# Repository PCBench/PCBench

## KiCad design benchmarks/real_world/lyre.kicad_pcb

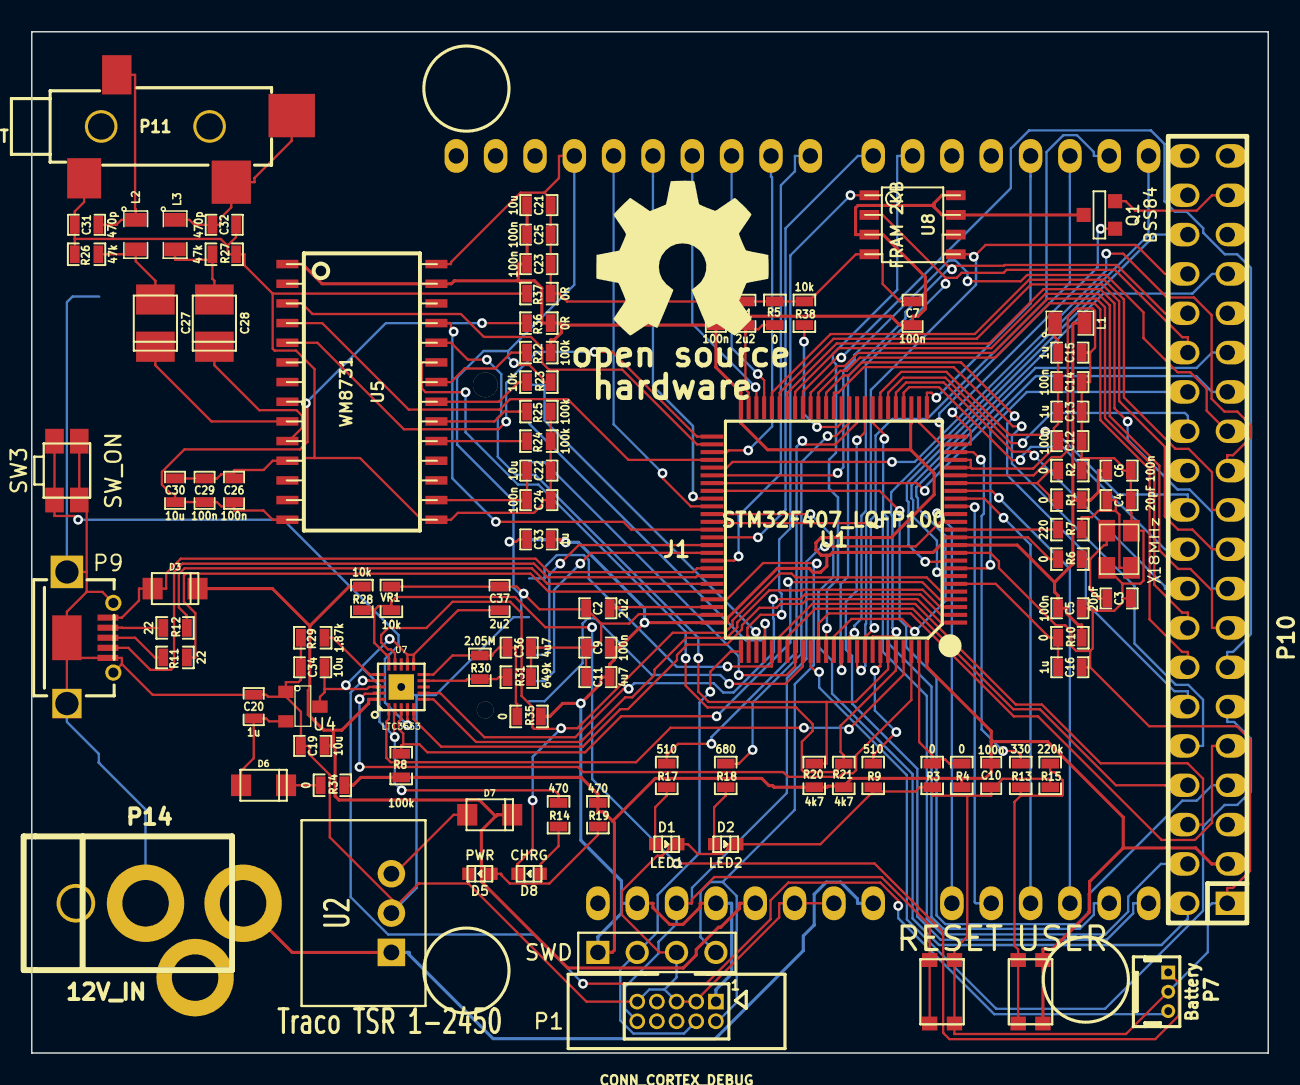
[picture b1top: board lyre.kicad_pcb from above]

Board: 2 copper layers, 79.9 x 66.0 mm, 101 parts (1 on the bottom side), 127 nets.

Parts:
C1, C2, C37: 2u2; SM0603_Capa
C3, C4: 20pF; SM0603_Capa
C5, C6, C7, C8, C9, C10, C12, C14, C23, C24, C25, C26, C29: 100n; SM0603_Capa
C11, C36: 4u7; SM0603_Capa
C13, C15, C16, C20, C33: 1u; SM0603_Capa
C19, C21, C22, C30, C34: 10u; SM0603_Capa
C27, C28: 220u; c_tant_B
C31, C32: 470p; SM0603_Capa
D1: LED1; Led_0603
D2: LED2; Led_0603
D3, D6, D7: DIODE; do219ab
D5: PWR; Led_0603
D8: CHRG; Led_0603
J1: ARDUINO_HEADER; arduino_header_bare
L1: L_MINI; SM0805
L2, L3: INDUCTOR_SMALL; SM0805
M1: LOGO_OSHW; OSHW_logo_2
P1: SWD; pin_header_2.54mm_1x4
P7: Battery; BATTery_Molex_53047-0310
P8: CONN_CORTEX_DEBUG; Pin_Array_5x2_1.27mm_RMC
P9: USBCONN-HOSTCAPABLE; USB_MICRO_RMC
P10: LCD_2.4_INCH; pin_socket_20x2
P11: STEREO-AUDIO-JACK_SJ1-3524-SMT; SJ-3524-SMT_Stereo_Jack
P13: CONN_SD; Memory_Card_SD_3M
P14: 12V_IN; JACK_PWR
Q1: BSS84; SOT23GDS
R1, R2, R3, R4, R5, R6, R10, R34, R35: 0; SM0603_Resistor
R7: 220; SM0603_Resistor
R8, R22, R24, R25: 100k; SM0603_Resistor
R9, R17: 510; SM0603_Resistor
R11, R12: 22; SM0603_Resistor
R13: 330; SM0603_Resistor
R14, R19: 470; SM0603_Resistor
R15: 220k; SM0603_Resistor
R18: 680; SM0603_Resistor
R20, R21: 4k7; SM0603_Resistor
R23, R28, R38: 10k; SM0603_Resistor
R26, R27: 47k; SM0603_Resistor
R29: 1.87k; SM0603_Resistor
R30: 2.05M; SM0603_Resistor
R31: 649k; SM0603_Resistor
R36, R37: 0R; SM0603_Resistor
SW1: USER; SW_C&K_KMR4
SW2: RESET; SW_C&K_KMR4
SW3: SW_ON; sw_panasonic_evqp7
U1: STM32F407_LQFP100; LQFP100_0.5mm_SOT407-1_LPC1768
U2: Traco TSR 1-2450; Traco_TSR-1
U4: MCP1703_SOT23; SOT23
U5: WM8731; soic-28
U7: LTC3553; qfn-20-LTC3553
U8: FRAM 2KB; so-8
VR1: 10k; SM0603_Resistor
X1: 8MHz; XTAL-3.2x2.5mm

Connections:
+5V: C19.1, D3.2, D7.2, J1.5, R28.1, U7.20
+12V: J1.8, P14.1, U2.1
/CPU/PB2: R38.2, U1.37
/CPU/VBAT: C16.1, R10.1, U1.6
/CPU/VDDA: C12.1, C13.1, C14.1, C15.1, L1.1, U1.21, U1.22
/LCD/LED_A: P10.37, Q1.S
/Power/BAT_THERMISTOR: P7.1, R28.2, U7.15, VR1.1
/Power/V_BAT: P7.3, U7.17
/Power/V_OUT: C34.1, C37.1, R14.1, U4.3, U7.2, U7.11, U7.12, U7.18
AGND_AUDIO: C22.2, C24.2, C26.2, C29.2, C30.2, C31.2, C32.2, P11.1, R24.1, R25.1, R26.2, R27.2, R37.2, U5.11, U5.15
AUDIO_SCL: R20.2, U1.95, U5.24
AUDIO_SDA: R21.2, U1.96, U5.23
AVDD: C26.1, C29.1, C30.1, R36.2, U5.8, U5.14
BOOT0: R9.1, U1.94
BTN_USER: R13.1, U1.23
BUCK_ON: U1.2, U7.7
D0: P10.2, U1.61
D1: P10.4, U1.62
D2: P10.6, U1.81
D3: P10.8, U1.82
D4: P10.10, U1.38
D5: P10.12, U1.39
D6: P10.14, U1.40
D7: P10.16, U1.41
D8: P10.13, U1.42
D9: P10.15, U1.43
D10: P10.17, U1.44
D11: P10.19, U1.45
D12: P10.21, U1.46
D13: P10.23, U1.55
D14: P10.25, U1.56
D15: P10.27, U1.57
GND: C1.2, C2.2, C3.2, C4.2, C5.2, C6.2, C7.2, C8.2, C9.2, C10.2, C11.2, C12.2, C13.2, C14.2, C15.2, C16.2, C19.2, C20.2, C21.2, C23.2, C25.2, C33.2, C34.2, C36.2, C37.2, D1.2, D2.2, D5.2, J1.6, J1.7, J1.29, P1.3, P7.2, P8.3, P8.5, P8.9, P9.4, P9.5, P10.1, P13.3, P13.6, P13.16, P13.17, P14.2, R2.2, R3.2, R5.2, R9.2, R15.2, R23.2, R29.2, R31.2, R37.1, R38.1, SW2.2, SW3.1, U1.10, U1.20, U1.27, U1.74, U2.2, U4.1, U5.28, U7.21, U8.4, VR1.2, X1.2, X1.4
HPWR: U1.97, U7.1
I2S_MCK: U1.63, U5.25
I2S_SCK: U1.52, U5.3
I2S_SD: U1.54, U5.4
I2S_WS: U1.51, U5.5
JTCK_SWCLK: P1.2, P8.4, U1.76
JTMS_SWDIO: P1.4, P8.2, U1.72
LCD_CS: P10.29, U1.88
LCD_RD: P10.11, U1.85
LCD_RS: P10.7, U1.58
LCD_RST: P10.33, U1.7
LCD_WR: P10.9, U1.86
LDO_ON: U1.1, U7.5
LED1: R17.1, U1.35
LED2: R18.1, U1.36
LED_PWM: Q1.G, U1.24
unnamed: R7.1, U1.13
unnamed: R6.1, U1.12
unnamed: C3.1, R6.2, X1.1
unnamed: C4.1, R7.2, X1.3
unnamed: R3.1, R4.1, U1.99
unnamed: R1.1, R2.1, U1.19
unnamed: C2.1, U1.73
unnamed: C1.1, R5.1, U1.49
unnamed: C31.1, L2.1, P11.3
unnamed: C28.1, U5.10
unnamed: C27.1, U5.9
unnamed: R24.2, U5.19
unnamed: R25.2, U5.20
unnamed: C28.2, L3.2, R27.1
unnamed: C27.2, L2.2, R26.1
unnamed: C32.1, L3.1, P11.2, P11.4
unnamed: C22.1, C24.1, U5.16
unnamed: R23.1, U5.21
unnamed: R22.2, U5.22
unnamed: D5.1, R19.2
unnamed: D6.2, R34.1
unnamed: R30.2, R31.1, U7.9
unnamed: SW3.2, U7.4
unnamed: R29.1, U7.16
unnamed: C20.1, D6.1, U4.2
unnamed: C36.1, R30.1, R35.1, U7.10
unnamed: D8.1, R14.2
unnamed: D7.1, U2.3
unnamed: P9.2, R12.1
unnamed: P9.3, R11.2
unnamed: R13.2, R15.1, SW1.2
unnamed: D1.1, R17.2
unnamed: D2.1, R18.2
NRST: J1.3, P8.10, SW2.1, U1.14
OTG_FS_DM: R12.2, U1.70
OTG_FS_DP: R11.1, U1.71
OTG_FS_ID: P9.6, U1.69
PA2: J1.17, U1.25
PA3: J1.18, U1.26
PA8: J1.23, U1.67
PB10: J1.25, U1.47
PB11: J1.26, U1.48
PB14: J1.24, U1.53
PBSTAT: R8.2, U1.4, U7.3
PC0: J1.9, U1.15
PC1: J1.10, U1.16
PC2: J1.11, U1.17
PC3: J1.12, U1.18
PC4: J1.13, U1.33
PC5: J1.14, U1.34
PC7: J1.22, U1.64
PD6: J1.21, U1.87
PD12: J1.27, U1.59
PD13: J1.28, U1.60
SDIO_CK: P13.5, U1.80
SDIO_CMD: P13.2, U1.83
SDIO_D0: P13.7, U1.65
SDIO_D1: P13.8, U1.66
SDIO_D2: P13.9, U1.78
SDIO_D3: P13.1, U1.79
SD_CARD_DET: P13.15, U1.84
SD_SS: P10.36, U1.9
SPI1_MISO: P10.26, U1.31
SPI1_MOSI: P10.22, U1.32
SPI1_SCK: P10.18, U1.30
SPI1_SS: P10.20, U1.29
SPI3_MISO: P10.30, U1.90, U8.2
SPI3_MOSI: P10.34, U1.91, U8.5
SPI3_SCK: P10.32, U1.89, U8.6
SPI3_SS: U1.77, U8.1
STBY: U1.3, U7.6
SUSP: U1.98, U7.19
TP_INT: P10.28, U1.8
UART1_RX: J1.15, U1.93
UART1_TX: J1.16, U1.92
VBUS_FS: D3.1, P9.1, U1.68
VDD: C5.1, C6.1, C7.1, C8.1, C9.1, C10.1, C11.1, C21.1, C23.1, C25.1, C33.1, J1.2, J1.4, L1.2, P1.1, P8.1, P10.3, P13.4, Q1.D, R1.2, R4.2, R8.1, R10.2, R19.1, R20.1, R21.1, R22.1, R34.2, R35.2, R36.1, SW1.1, U1.11, U1.28, U1.50, U1.75, U1.100, U5.1, U5.27, U8.3, U8.7, U8.8
nCHRG: D8.2, U1.5, U7.14

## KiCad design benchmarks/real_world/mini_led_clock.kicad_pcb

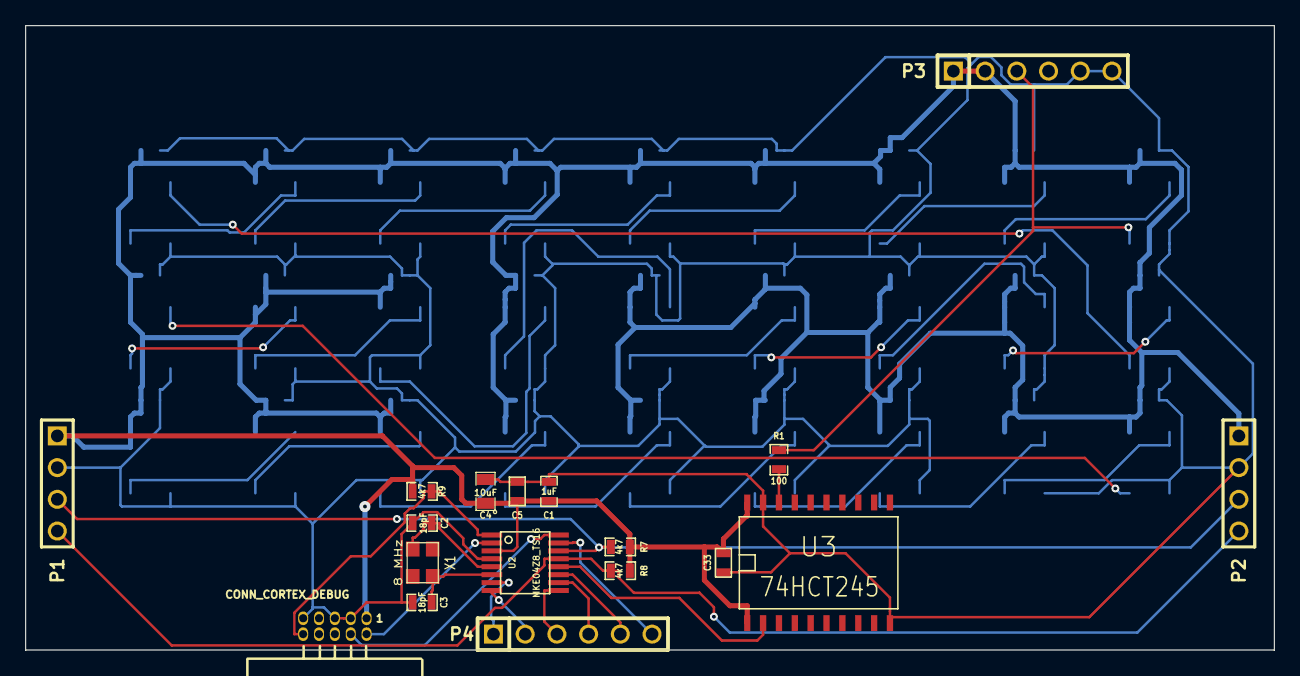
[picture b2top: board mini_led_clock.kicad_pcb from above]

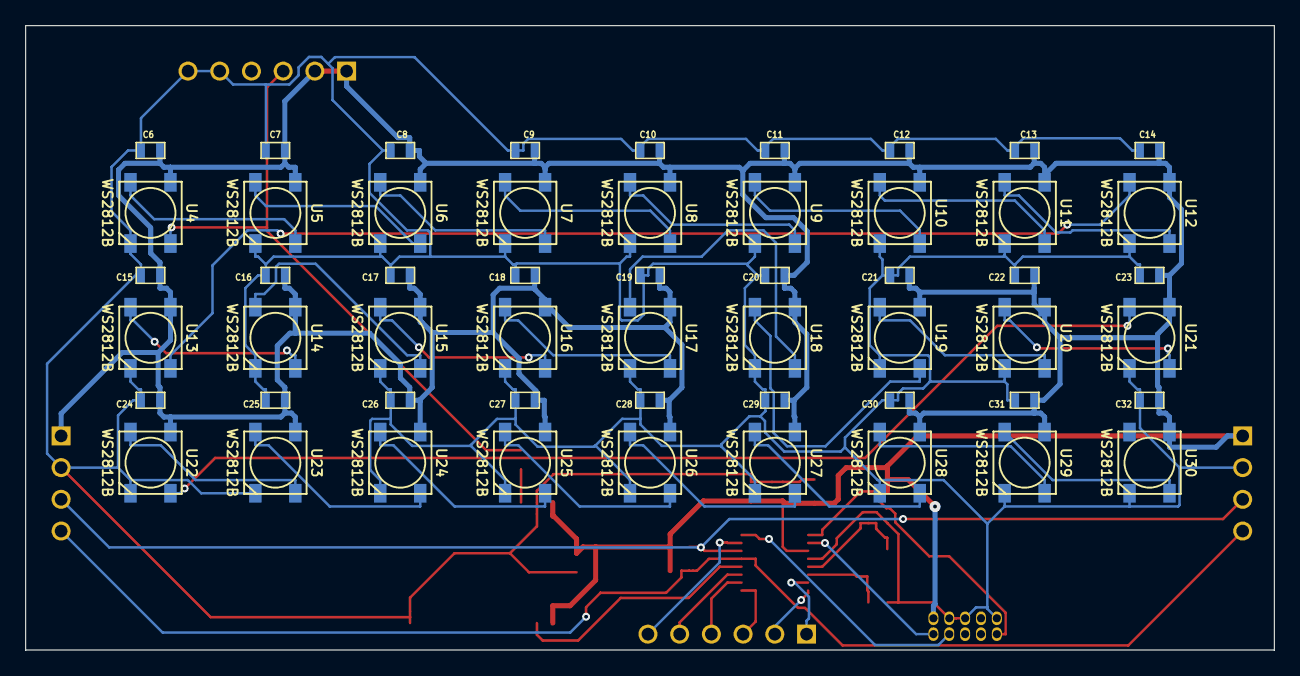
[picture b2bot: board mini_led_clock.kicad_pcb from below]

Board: 2 copper layers, 100.0 x 50.0 mm, 72 parts (54 on the bottom side), 44 nets.

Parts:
C1: 1uF; SM0603_Capa
C2, C3: 18pF; SM0603_Capa
C4: 10uF; SM0805
C5, C6, C7, C8, C9, C10, C11, C12, C13, C14, C15, C16, C17, C18, C19, C20, C21, C22, C23, C24, C25, C26, C27, C28, C29, C30, C31, C32, C33: 100nF; SM0603
P1, P2: CONN_4; PIN_ARRAY_4x1
P3, P4: CONN_6; PIN_ARRAY-6X1
R1: 100; SM0603_Resistor
R7, R8, R9: 4k7; SM0603_Resistor
U1: CONN_CORTEX_DEBUG; Pin_Array_5x2_1.27mm_RA_RMC
U2: MKE04Z8_TS16; ssop-16
U3: 74HCT245; SO20L
U4, U5, U6, U7, U8, U9, U10, U11, U12, U13, U14, U15, U16, U17, U18, U19, U20, U21, U22, U23, U24, U25, U26, U27, U28, U29, U30: WS2812B
X1: 8 MHz; XTAL-3.2x2.5mm

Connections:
/A1: P4.6, U2.15
/B1: P4.5, U2.11
/B2: P4.4, U2.10
/B3: P4.3, U2.9
/B4: P4.2, U2.8
/B5: P4.1, U2.7
/EXTAL: C2.2, U2.5, X1.1
/SCL: P1.4, P2.4, R8.1, U2.13
/SDA: P1.3, P2.3, R7.1, U2.14
/SWD_CLK: U1.4, U2.16
/SWD_DIO: U1.2, U2.2
/XTAL: C3.2, U2.6, X1.3
/nRESET: R9.1, U1.10, U2.1
GND: C1.2, C2.1, C3.1, C4.2, C5.2, C6.2, C7.2, C8.2, C9.2, C10.2, C11.2, C12.2, C13.2, C14.2, C15.2, C16.2, C17.2, C18.2, C19.2, C20.2, C21.2, C22.2, C23.2, C24.2, C25.2, C26.2, C27.2, C28.2, C29.2, C30.2, C31.2, C32.2, C33.2, P1.2, P2.2, P3.5, P3.6, U1.3, U1.5, U1.9, U2.4, U3.10, U3.19, U4.3, U5.3, U6.3, U7.3, U8.3, U9.3, U10.3, U11.3, U12.3, U13.3, U14.3, U15.3, U16.3, U17.3, U18.3, U19.3, U20.3, U21.3, U22.3, U23.3, U24.3, U25.3, U26.3, U27.3, U28.3, U29.3, U30.3
LED_DATA: P3.3, R1.2, U4.4
unnamed: R1.1, U3.18
unnamed: U2.12, U3.2
unnamed: U22.2, U23.4
unnamed: U23.2, U24.4
unnamed: U21.2, U22.4
unnamed: U19.2, U20.4
unnamed: U20.2, U21.4
unnamed: U18.2, U19.4
unnamed: U29.2, U30.4
unnamed: U27.2, U28.4
unnamed: U28.2, U29.4
unnamed: U24.2, U25.4
unnamed: U25.2, U26.4
unnamed: U26.2, U27.4
unnamed: U9.2, U10.4
unnamed: U8.2, U9.4
unnamed: U6.2, U7.4
unnamed: U7.2, U8.4
unnamed: U10.2, U11.4
unnamed: U5.2, U6.4
unnamed: U4.2, U5.4
unnamed: U14.2, U15.4
unnamed: U17.2, U18.4
unnamed: U15.2, U16.4
unnamed: U16.2, U17.4
unnamed: U12.2, U13.4
unnamed: U11.2, U12.4
unnamed: U13.2, U14.4
VCC: C1.1, C4.1, C5.1, C6.1, C7.1, C8.1, C9.1, C10.1, C11.1, C12.1, C13.1, C14.1, C15.1, C16.1, C17.1, C18.1, C19.1, C20.1, C21.1, C22.1, C23.1, C24.1, C25.1, C26.1, C27.1, C28.1, C29.1, C30.1, C31.1, C32.1, C33.1, P1.1, P2.1, P3.1, P3.2, R7.2, R8.2, R9.2, U1.1, U2.3, U3.1, U3.20, U4.1, U5.1, U6.1, U7.1, U8.1, U9.1, U10.1, U11.1, U12.1, U13.1, U14.1, U15.1, U16.1, U17.1, U18.1, U19.1, U20.1, U21.1, U22.1, U23.1, U24.1, U25.1, U26.1, U27.1, U28.1, U29.1, U30.1

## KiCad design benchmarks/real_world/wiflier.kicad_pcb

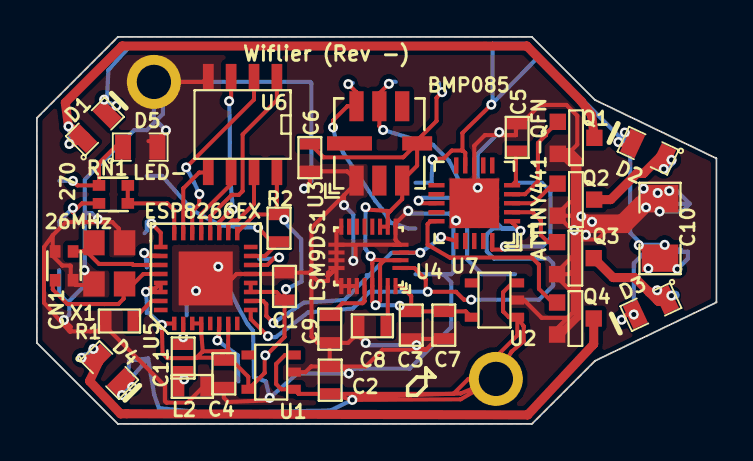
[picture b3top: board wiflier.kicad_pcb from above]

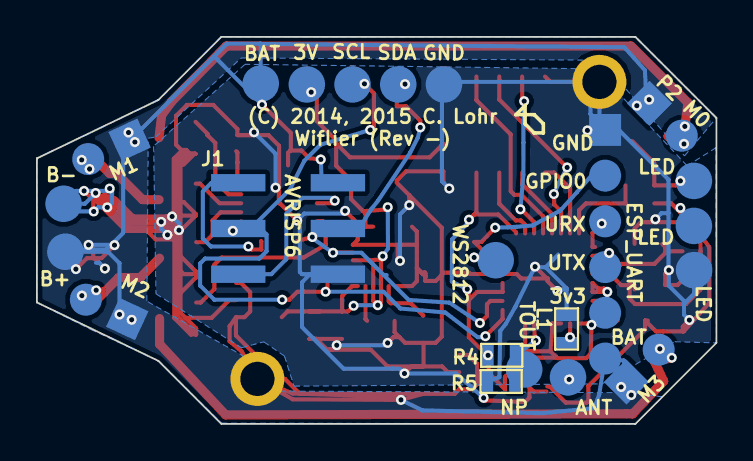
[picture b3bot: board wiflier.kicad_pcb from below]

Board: 2 copper layers, 37.8 x 21.5 mm, 57 parts (22 on the bottom side), 38 nets.

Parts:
C1, C2, C3: 10uF; SM0603
C4: 1uF; SM0603
C5: 1u; SM0603
C6, C7, C8: .1u; SM0603
C9: 10nF; SM0603
C10: 100uF; SM1206
C11: 5.6pF; SM0603
CN1: 10p; NETWORK0606
D1, D2, D3, D4: 20V_500mA; SM0805
D5: LED-; SM0805
J1: AVRISP6; RIBBON6SMT
L1, L2: NP; SM0603
P1: WS2812; .1SMTPIN
P2: M0; SMT_1x2
P3: M1; SMT_1x2
P4: M2; SMT_1x2
P5: M3; SMT_1x2
P6: ANT; .1SMTPIN
P7, P8: HOLE-1.9MM
P9: SDA; .1SMTPIN
P10: SCL; .1SMTPIN
P11: 3V; .1SMTPIN
P12: GND; .1SMTPIN
P13, P14, P15: LED; .1SMTPIN
P16: BAT; .1SMTPIN
P17: TOUT; .1SMTPIN
P21: B+; .1SMTPIN
P24: B-; .1SMTPIN
P32: ESP_UART; SMT_1x6
Q1, Q2, Q3, Q4: 7A_20V; SOT23GDS
R1, R2, R4: 12k; SM0603
R5: NP; SM0603
RN1: 270; NETWORK0606
U1, U2: MCP1824/3.0; SOT23-5
U3: BMP085
U4: LSM9DS1; LGA-24B
U5: ESP8266EX; QFN32
U6: W25Q80DV; SO8E
U7: ATTINY441-QFN; QFN20
X1: 26MHz; XTAL4P

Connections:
+3.3V: C1.1, C4.1, P32.5, R2.2, R4.1, U1.5, U5.1, U5.3, U5.4, U5.7, U5.11, U5.12, U5.17, U5.29, U5.30, U6.8
+3.3VP: C3.1, C6.2, C7.1, P11.1, U2.5, U3.3, U3.4, U4.1, U4.3, U4.7, U4.8, U4.22, U4.23
+BATT: C2.1, C10.1, D1.2, D2.2, D3.2, D4.2, J1.2, P2.1, P3.1, P4.1, P5.1, P8.1, P16.1, P21.1, P32.6, U1.1, U1.3, U2.1, U2.3, U7.9
AVRMISO: J1.1, U7.20
AVRRST: J1.5, U7.13
GND: C1.2, C2.2, C3.2, C4.2, C5.1, C6.1, C7.2, C8.1, C9.1, C10.2, CN1.2, CN1.3, D5.2, J1.6, L1.2, L2.2, P7.1, P12.1, P15.1, P24.1, P32.1, Q1.S, Q2.S, Q3.S, Q4.S, R1.1, R5.2, U1.2, U2.2, U3.1, U4.5, U4.6, U4.13, U4.14, U4.15, U4.16, U4.17, U4.18, U4.19, U4.20, U5.13, U5.33, U6.4, U7.8, U7.21, X1.3, X1.4
GP5: RN1.1, RN1.3, U5.24
GPIO0: P32.2, R2.1, U5.15
GPIO2: P1.1, U5.14
M0P: D1.1, P2.2, Q1.D
M1P: D2.1, P3.2, Q2.D
M2P: D3.1, P4.2, Q3.D
M3P: D4.1, P5.2, Q4.D
MTR0: Q1.G, U7.4
MTR1: Q2.G, U7.3
MTR2: Q3.G, U7.2
MTR3: Q4.G, U7.15
unnamed: C11.1, L1.1, U5.2
unnamed: C11.2, L2.1, P6.1
unnamed: CN1.1, U5.28, X1.2
unnamed: R1.2, U5.31
unnamed: CN1.4, U5.27, X1.1
unnamed: C8.2, U4.24
unnamed: C9.2, U4.21
unnamed: P13.1, RN1.2
unnamed: D5.1, P14.1, RN1.4
unnamed: C5.2, U7.5
unnamed: U5.22, U6.2
unnamed: U5.23, U6.5
unnamed: U5.19, U6.3
unnamed: U5.18, U6.7
unnamed: U5.20, U6.1
unnamed: U5.21, U6.6
SCL: J1.3, P10.1, U3.6, U4.2, U5.9, U7.1
SDA: J1.4, P9.1, U3.7, U4.4, U5.10, U7.16
TOUT: P17.1, R4.2, R5.1, U5.6
URX: P32.3, U5.25
UTX: P32.4, U5.26

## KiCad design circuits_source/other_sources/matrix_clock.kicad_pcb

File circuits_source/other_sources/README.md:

This folder contains circuit source files from any other sources except Adafruit, Sparkfun, Crowdsupply and Kitspace. Note that if the souce file is from KiCAD version 5, please put `.kicad_pcb` file in this folder, and if the source file is from KiCAD version 6, please put `.kicad_pcb` and `.pro` file in this folder.

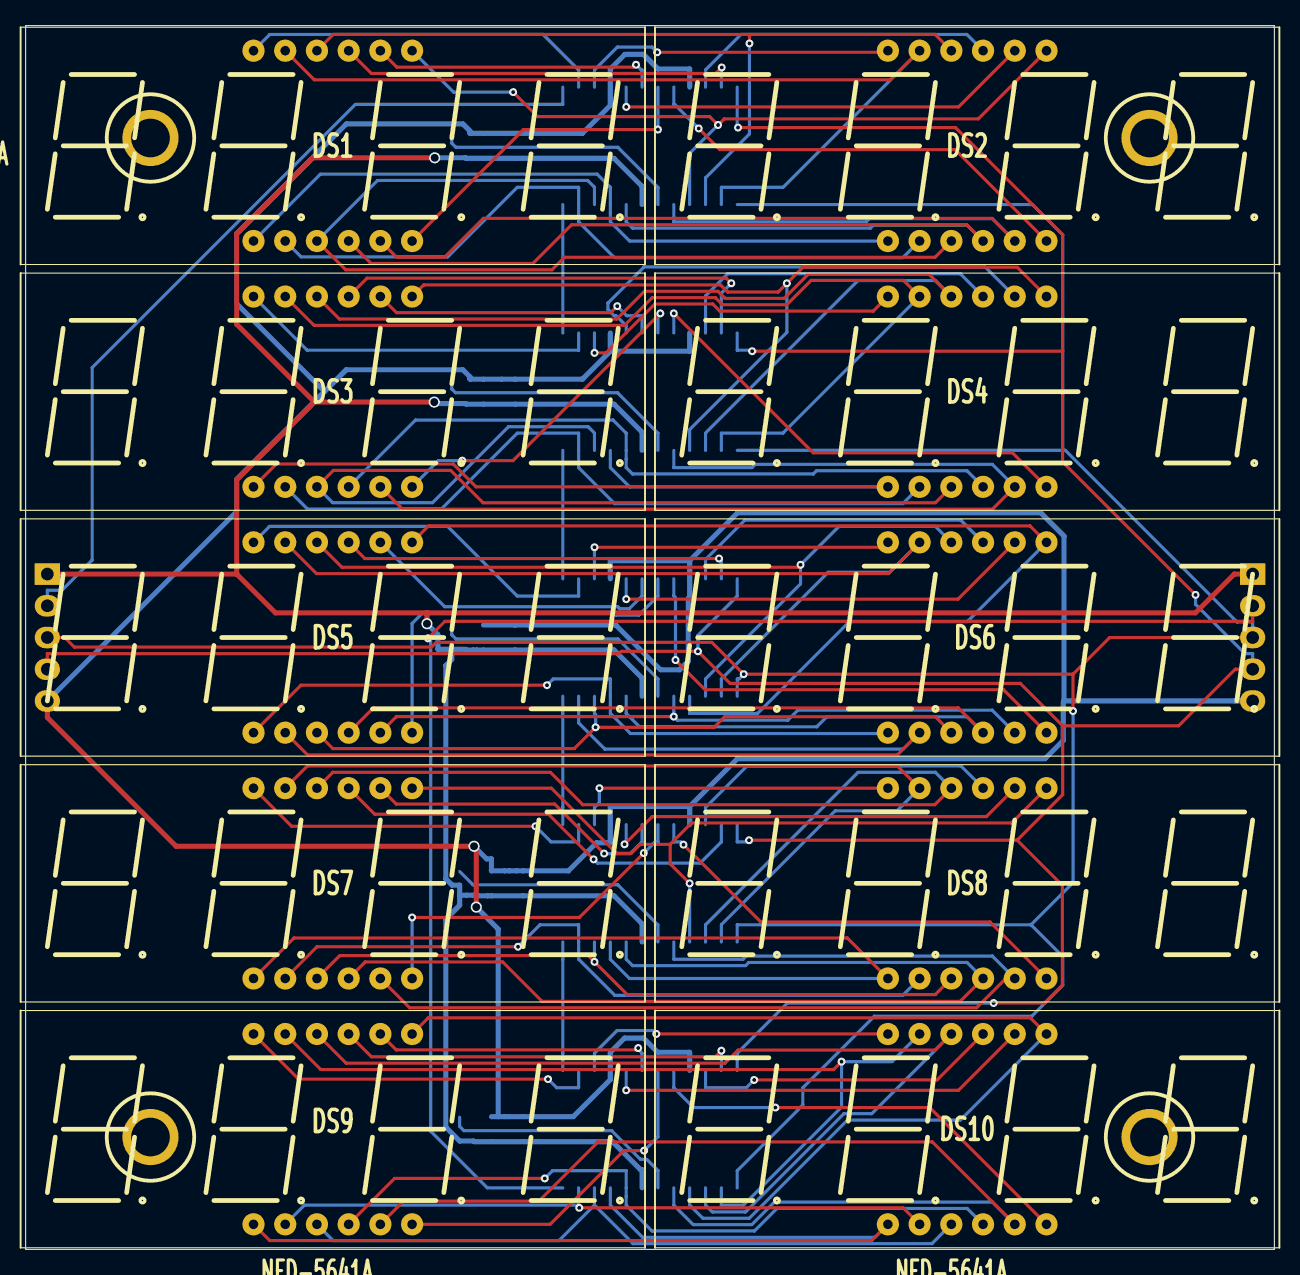
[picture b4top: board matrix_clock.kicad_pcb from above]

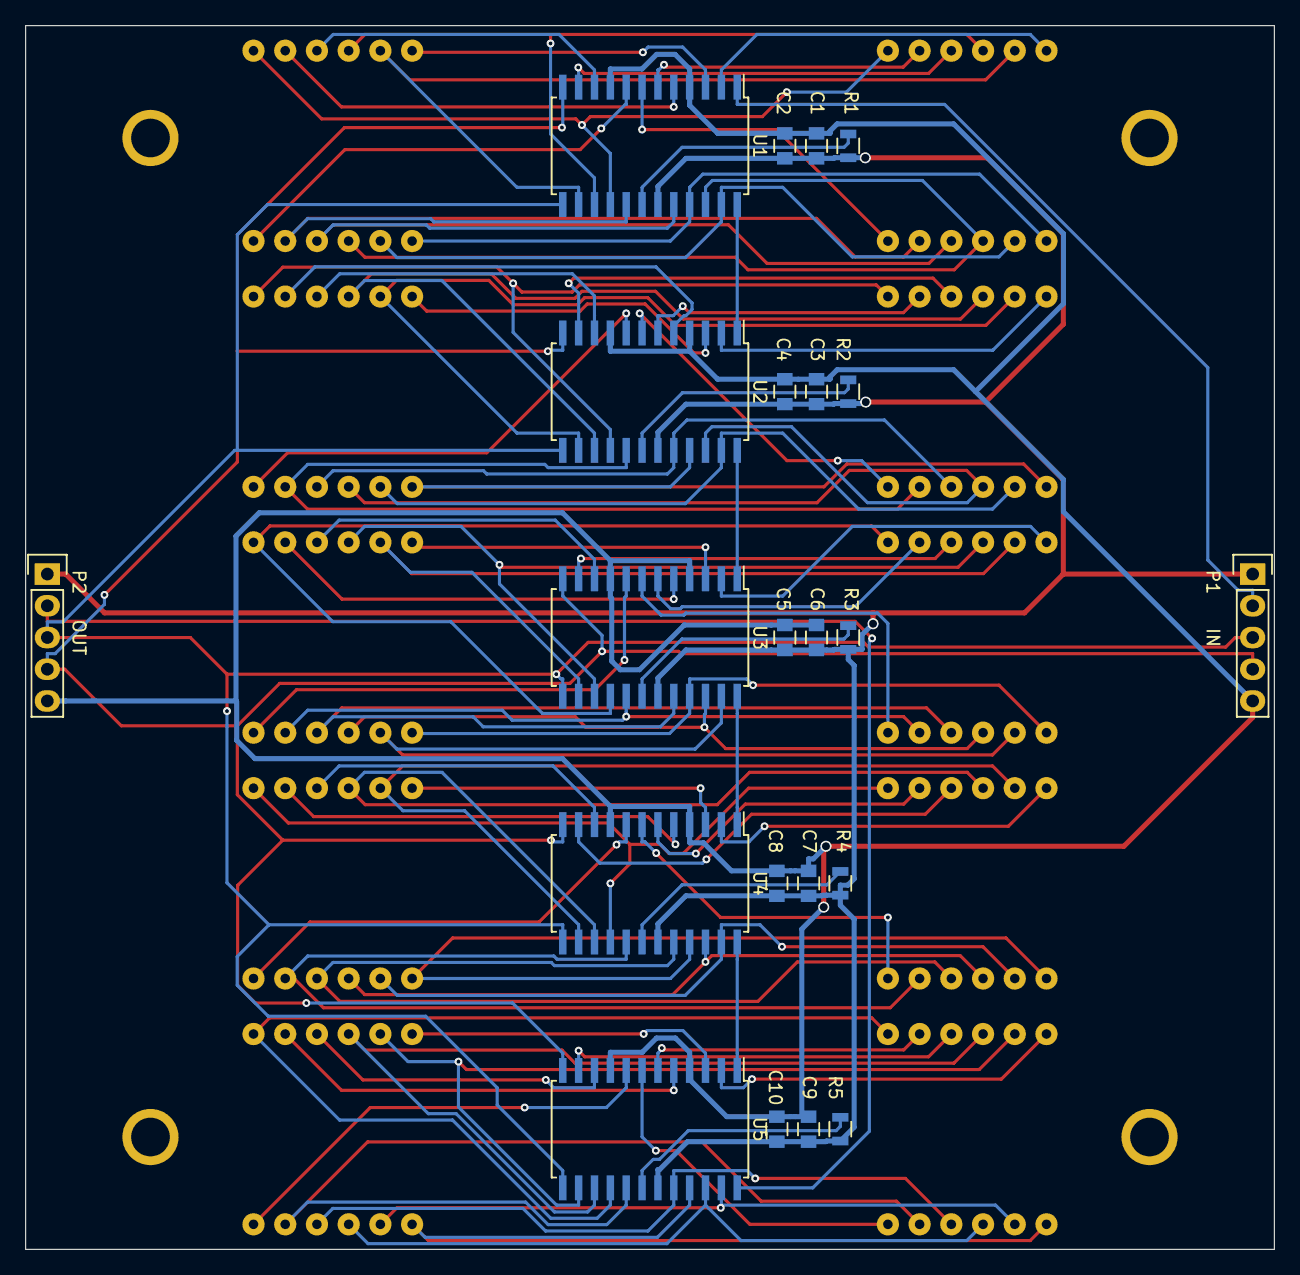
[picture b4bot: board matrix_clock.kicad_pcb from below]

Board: 2 copper layers, 100.0 x 98.0 mm, 36 parts (22 on the bottom side), 95 nets.

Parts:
C1, C3, C5, C7, C9: 10uF; C_0805
C2, C4, C6, C8, C10: 100nF; C_0805
DS1, DS2, DS3, DS4, DS5, DS6, DS7, DS8, DS9, DS10: NFD-5641A; NFD-5641
H1, H2, H3, H4: HOLE_RMC; HOLE_M3
P1: IN; Socket_Strip_Straight_1x05
P2: OUT; Socket_Strip_Straight_1x05
R1, R2, R3, R4, R5: 28k; R_0805
U1, U2, U3, U4, U5: MAX7219; SOIC-24_7.5x15.4mm_Pitch1.27mm

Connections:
/Digits Row 1/CLK: P1.3, P2.3, U1.13, U2.13, U3.13, U4.13, U5.13
/Digits Row 1/DIN: P1.2, U1.1
/Digits Row 1/LOAD: P1.4, P2.4, U1.12, U2.12, U3.12, U4.12, U5.12
/Digits Row 1/SEG_A: DS1.11, DS2.11, U1.14
/Digits Row 1/SEG_B: DS1.7, DS2.7, U1.16
/Digits Row 1/SEG_C: DS1.4, DS2.4, U1.20
/Digits Row 1/SEG_D: DS1.2, DS2.2, U1.23
/Digits Row 1/SEG_DP: DS1.3, DS2.3, U1.22
/Digits Row 1/SEG_E: DS1.1, DS2.1, U1.21
/Digits Row 1/SEG_F: DS1.10, DS2.10, U1.15
/Digits Row 1/SEG_G: DS1.5, DS2.5, U1.17
/Row 2/DIN: U1.24, U2.1
/Row 2/SEG_A: DS3.11, DS4.11, U2.14
/Row 2/SEG_B: DS3.7, DS4.7, U2.16
/Row 2/SEG_C: DS3.4, DS4.4, U2.20
/Row 2/SEG_D: DS3.2, DS4.2, U2.23
/Row 2/SEG_DP: DS3.3, DS4.3, U2.22
/Row 2/SEG_E: DS3.1, DS4.1, U2.21
/Row 2/SEG_F: DS3.10, DS4.10, U2.15
/Row 2/SEG_G: DS3.5, DS4.5, U2.17
/Row 3/DIN: U2.24, U3.1
/Row 3/SEG_A: DS5.11, DS6.11, U3.14
/Row 3/SEG_B: DS5.7, DS6.7, U3.16
/Row 3/SEG_C: DS5.4, DS6.4, U3.20
/Row 3/SEG_D: DS5.2, DS6.2, U3.23
/Row 3/SEG_DP: DS5.3, DS6.3, U3.22
/Row 3/SEG_E: DS5.1, DS6.1, U3.21
/Row 3/SEG_F: DS5.10, DS6.10, U3.15
/Row 3/SEG_G: DS5.5, DS6.5, U3.17
/Row 4/DIN: U3.24, U4.1
/Row 4/SEG_A: DS7.11, DS8.11, U4.14
/Row 4/SEG_B: DS7.7, DS8.7, U4.16
/Row 4/SEG_C: DS7.4, DS8.4, U4.20
/Row 4/SEG_D: DS7.2, DS8.2, U4.23
/Row 4/SEG_DP: DS7.3, DS8.3, U4.22
/Row 4/SEG_E: DS7.1, DS8.1, U4.21
/Row 4/SEG_F: DS7.10, DS8.10, U4.15
/Row 4/SEG_G: DS7.5, DS8.5, U4.17
/Row 5/DIN: U4.24, U5.1
/Row 5/DOUT: P2.2, U5.24
/Row 5/SEG_A: DS9.11, DS10.11, U5.14
/Row 5/SEG_B: DS9.7, DS10.7, U5.16
/Row 5/SEG_C: DS9.4, DS10.4, U5.20
/Row 5/SEG_D: DS9.2, DS10.2, U5.23
/Row 5/SEG_DP: DS9.3, DS10.3, U5.22
/Row 5/SEG_E: DS9.1, DS10.1, U5.21
/Row 5/SEG_F: DS9.10, DS10.10, U5.15
/Row 5/SEG_G: DS9.5, DS10.5, U5.17
GND: C1.2, C2.2, C3.2, C4.2, C5.2, C6.2, C7.2, C8.2, C9.2, C10.2, P1.5, P2.5, U1.4, U1.9, U2.4, U2.9, U3.4, U3.9, U4.4, U4.9, U5.4, U5.9
unnamed: DS1.6, U1.7
unnamed: DS1.8, U1.6
unnamed: DS1.9, U1.11
unnamed: DS1.12, U1.2
unnamed: DS2.6, U1.8
unnamed: DS2.8, U1.5
unnamed: DS2.9, U1.10
unnamed: DS2.12, U1.3
unnamed: DS3.6, U2.7
unnamed: DS3.8, U2.6
unnamed: DS3.9, U2.11
unnamed: DS3.12, U2.2
unnamed: DS4.6, U2.8
unnamed: DS4.8, U2.5
unnamed: DS4.9, U2.10
unnamed: DS4.12, U2.3
unnamed: DS5.6, U3.7
unnamed: DS5.8, U3.6
unnamed: DS5.9, U3.11
unnamed: DS5.12, U3.2
unnamed: DS6.6, U3.8
unnamed: DS6.8, U3.5
unnamed: DS6.9, U3.10
unnamed: DS6.12, U3.3
unnamed: DS7.6, U4.7
unnamed: DS7.8, U4.6
unnamed: DS7.9, U4.11
unnamed: DS7.12, U4.2
unnamed: DS8.6, U4.8
unnamed: DS8.8, U4.5
unnamed: DS8.9, U4.10
unnamed: DS8.12, U4.3
unnamed: DS9.6, U5.7
unnamed: DS9.8, U5.6
unnamed: DS9.9, U5.11
unnamed: DS9.12, U5.2
unnamed: DS10.6, U5.8
unnamed: DS10.8, U5.5
unnamed: DS10.9, U5.10
unnamed: DS10.12, U5.3
unnamed: R1.2, U1.18
unnamed: R2.2, U2.18
unnamed: R3.2, U3.18
unnamed: R4.2, U4.18
unnamed: R5.2, U5.18
VCC: C1.1, C2.1, C3.1, C4.1, C5.1, C6.1, C7.1, C8.1, C9.1, C10.1, P1.1, P2.1, R1.1, R2.1, R3.1, R4.1, R5.1, U1.19, U2.19, U3.19, U4.19, U5.19

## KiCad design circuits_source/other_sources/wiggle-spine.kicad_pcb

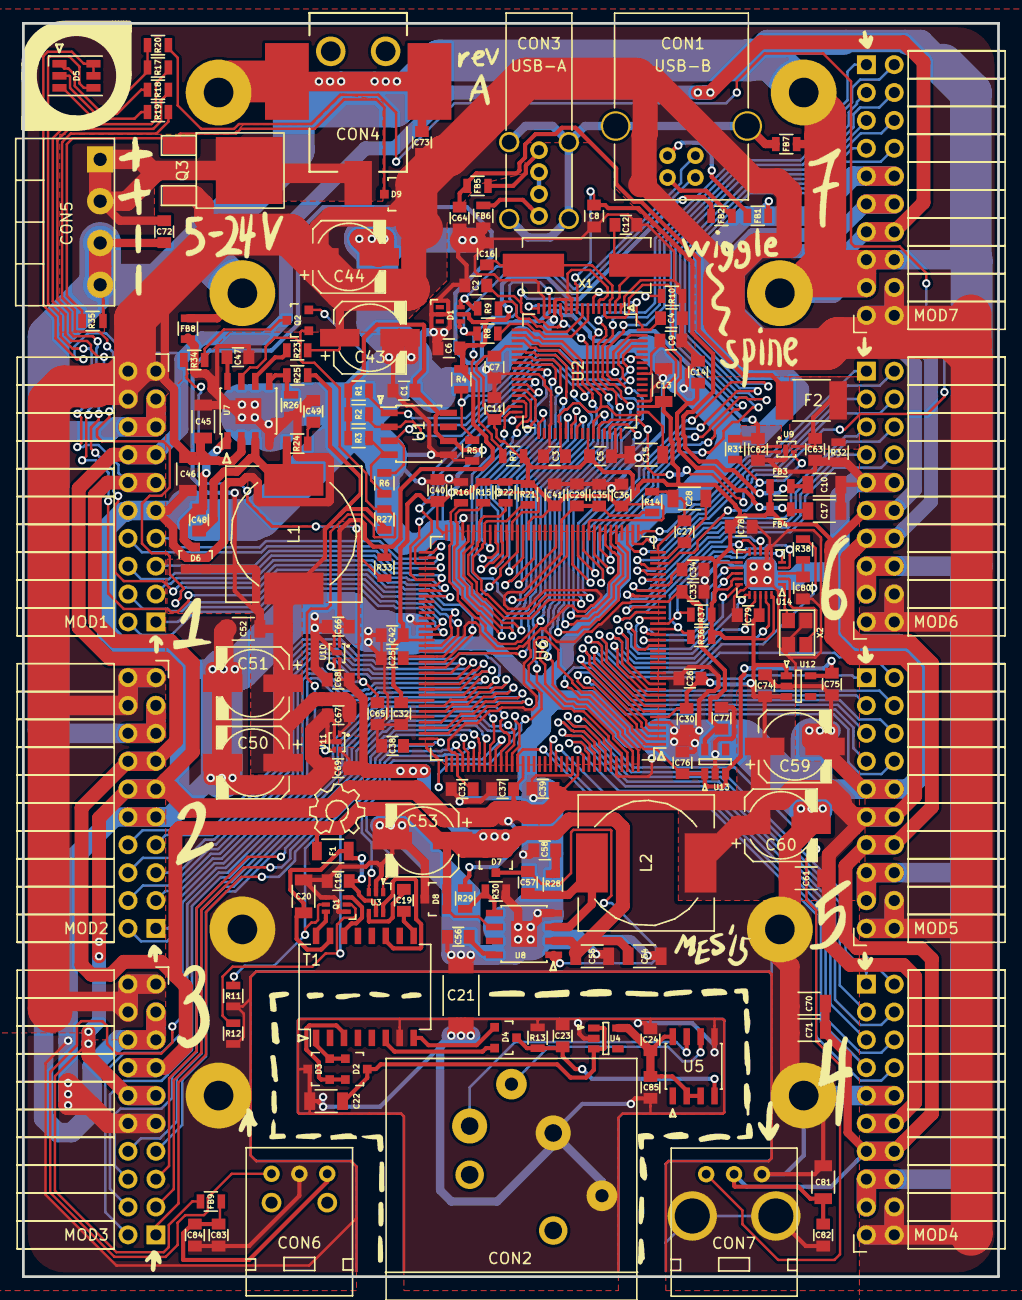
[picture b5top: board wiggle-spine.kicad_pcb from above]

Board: 2 copper layers, 88.9 x 114.3 mm, 179 parts (0 on the bottom side), 172 nets.

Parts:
C1, C2, C3, C4, C5, C6, C7, C8, C9, C11, C14, C18, C25, C26, C27, C29, C30, C31, C32, C33, C34, C35, C36, C37, C38, C39, C40, C41, C42, C48, C57, C63, C64, C65, C68, C69, C72, C74, C76, C78, C79, C82, C83, C85: 0.1uF; C_0805
C10, C13, C15, C17, C20, C22, C28, C45, C46, C52, C54, C55, C61, C70, C71, C81: 10uF; C_1206
C12, C16: 20pF; C_0805
C19, C23: 1nF; C_0805
C21: 1nF; C_1808
C24, C47, C56, C62, C66, C67, C73, C75, C77, C80, C84: 1uF; C_0805
C43, C44, C50, C51, C53, C59, C60: 22uF; c_elec_6.3x7.7
C49, C58: 100pF; C_0805
CON1: USB-B; USB_B
CON2: XLR-3 Female; XLR3MC
CON3: USB-A; USB_A_Vertical
CON4: 2.5mm 5-24V 5A; BARREL_JACK
CON5: 5-24V 16A; TerminalBlock_Pheonix_PT-3.5mm_4pol
CON6: PLR135; Everlight-PLR135-T8
CON7: PLT133; Everlight-PLT133-T6A
D1: TVS DIODE 5.5VWM; SC-70-6
D2, D4, D6, D7: BAT54 2x common cathode; SOT-23
D3: BAT54 2x common anode; SOT-23
D5: LED_BGR; LED_RGB_PLLC-6
D8, D9: 8.5VWM; SOT-23
F1: 200mA PTC; R_1206
F2: 2A PTC; R_1812
FB1, FB2, FB3, FB4, FB5, FB6, FB7, FB8, FB9: Ferrite bead; R_0805
L1, L2: 22uH; COIL_SMD_6mm_1mmCrtYd
MOD1, MOD2, MOD3, MOD4, MOD5, MOD6, MOD7: 2.54mm 2x10 right angle female header; Socket_Strip_Angled_2x10_Mirror
Q1: DMN3190LDW; SC-70-6
Q2: 2N7002P; SOT-23
Q3: AOD4189; TO-252-2Lead
R1, R2, R3, R5, R11, R12, R15, R16, R21, R22, R38: 10k; R_0805
R4, R7: 4.7k; R_0805
R6, R34, R36, R37: 2.2k; R_0805
R8, R9: 10; R_0805
R10: 12k 1%; R_0805
R13, R19: 240; R_0805
R14, R24, R28: 150; R_0805
R17, R18: 750; R_0805
R20, R29: 16k 1%; R_0805
R23, R27, R31, R32, R33, R35: 100k; R_0805
R25: 27k 1%; R_0805
R26, R30: 5.1k 1%; R_0805
T1: 10/100baseT transformer; SOIC-16_7.5x10.3mm_Pitch1.27mm
U1: 93C56; SOIC-8_3.9x4.9mm_Pitch1.27mm
U2: FT2232H; LQFP-64_10x10mm_Pitch0.5mm
U3: NC7WZ14; SC-70-6
U4: AP2204K-5.0; SOT-23-5
U5: ST485E; SOIC-8_3.9x4.9mm_Pitch1.27mm
U6: iCE40-HX1K-TQ144; TQFP-144_20x20mm_Pitch0.5mm
U7, U8: RT8299A; SOIC-8-1EP_3.9x4.9mm_Pitch1.27mm
U9, U10, U11: SiP32408; TDFN4
U12: TCR2EF25; SOT-23-5
U13: TCR2EF12; SOT-23-5
U14: Si5351B; QFN-20-1EP_4x4mm_Pitch0.5mm
X1: 12 MHz; Crystal_HC49-SD_SMD
X2: 25.0000 MHz 15ppm 8pF; crystal_FA238-TSX3225

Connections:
+1V2: C25.2, C29.2, C31.2, C33.2, C35.2, C77.1, R14.2, U6.27, U6.51, U6.92, U6.111, U13.5
+2V5: C38.2, C75.1, C76.2, U6.108, U12.5, U13.1, U13.3
+3V3: C1.2, C5.2, C7.2, C9.2, C11.2, C13.1, C26.2, C30.2, C32.2, C34.2, C36.2, C37.2, C39.2, C40.2, C41.2, C42.2, C59.1, C60.1, C61.1, C74.2, C78.2, C79.2, D5.4, FB3.1, FB4.1, FB9.1, L2.2, MOD1.11, MOD1.12, MOD2.11, MOD2.12, MOD3.11, MOD3.12, MOD4.11, MOD4.12, MOD5.11, MOD5.12, MOD6.11, MOD6.12, MOD7.11, MOD7.12, R1.2, R2.2, R3.2, R7.2, R15.2, R21.2, R22.2, R29.2, R36.1, R37.1, U1.6, U1.8, U2.20, U2.31, U2.42, U2.50, U2.56, U6.6, U6.30, U6.46, U6.57, U6.72, U6.89, U6.100, U6.123, U6.133, U12.1, U12.3, U14.10, U14.11, U14.14, U14.18, U14.20
+5V: C53.1, C54.1, C55.1, C68.2, C69.2, C70.1, C71.1, C81.1, C82.2, CON7.2, D5.5, D5.6, D7.1, D7.2, D8.1, D8.2, F1.2, MOD1.13, MOD1.14, MOD2.13, MOD2.14, MOD3.13, MOD3.14, MOD4.13, MOD4.14, MOD5.13, MOD5.14, MOD6.13, MOD6.14, MOD7.13, MOD7.14, U8.2, U8.6, U10.4, U11.4
+24V: C43.1, C44.1, C45.1, C46.1, C73.1, D9.1, D9.2, MOD1.18, MOD1.19, MOD1.20, MOD2.18, MOD2.19, MOD2.20, MOD3.18, MOD3.19, MOD3.20, MOD4.18, MOD4.19, MOD4.20, MOD5.18, MOD5.19, MOD5.20, MOD6.18, MOD6.19, MOD6.20, MOD7.18, MOD7.19, MOD7.20, Q3.3, R23.1, U7.2
/Clock Source/CLK0: U6.20, U14.13
/Clock Source/CLK1: U6.21, U14.12
/Clock Source/CLK2: U6.25, U14.9
/Clock Source/CLK3: U6.26, U14.8
/Clock Source/CLK4: U6.11, U14.19
/Clock Source/CLK5: U6.12, U14.17
/Clock Source/CLK6: U6.19, U14.16
/Clock Source/CLK7: U6.24, U14.15
/Clock Source/VCXO_PWM: R38.1, U6.10
/DMX512/DMXGND: C21.1, C22.2, C23.2, C24.2, C85.1, CON2.1, CON2.G, D3.3, R13.1, T1.7, U4.2, U5.5
/FPGA/BLUE_N: R17.1, U6.81
/FPGA/CDONE: R20.2, R21.1, U2.44, U6.65
/FPGA/CLK_SCL: R36.2, U6.22, U14.4
/FPGA/CLK_SDA: R37.2, U6.23, U14.5
/FPGA/CRESET_B: R22.1, U2.46, U6.66
/FPGA/DMX_GATE1: Q1.2, R12.1, U6.112
/FPGA/DMX_GATE2: Q1.5, R11.1, U6.107
/FPGA/DMX_TX1: U3.1, U6.118
/FPGA/DMX_TX2: U3.3, U6.114
/FPGA/FIFO_CLKOUT: U2.32, U6.50
/FPGA/FIFO_DATA0: U2.16, U6.142
/FPGA/FIFO_DATA1: U2.17, U6.141
/FPGA/FIFO_DATA2: U2.18, U6.42
/FPGA/FIFO_DATA3: U2.19, U6.94
/FPGA/FIFO_DATA4: U2.21, U6.52
/FPGA/FIFO_DATA5: U2.22, U6.56
/FPGA/FIFO_DATA6: U2.23, U6.58
/FPGA/FIFO_DATA7: U2.24, U6.61
/FPGA/FIFO_OE#: U2.33, U6.60
/FPGA/FIFO_RD#: U2.28, U6.64
/FPGA/FIFO_RXF#: U2.26, U6.75
/FPGA/FIFO_SIWU: U2.30, U6.78
/FPGA/FIFO_TXE#: U2.27, U6.62
/FPGA/FIFO_WR#: U2.29, U6.63
/FPGA/GREEN_N: R18.1, U6.90
/FPGA/RED_N: R19.1, U6.93
/FPGA/SYNC_TXD: CON7.3, U6.139
/FPGA/VBUS_DOWNSTREAM_EN: R31.1, U6.34, U9.3
/Power/5-24V Power Input/POWER_IN: C72.2, CON4.1, CON5.1, CON5.2, Q3.2
/Power/5-24V to 5V Converter/CONVERTED_5V_OKAY: Q2.1, R27.1, U7.7, U11.3
/Power/USB Power Output/5V_IN: C50.1, C51.1, C52.1, C62.1, C67.1, D6.1, D6.2, L1.2, R25.2, R27.2, R31.2, U9.1, U11.1
/Power/VBUS_UPSTREAM: C6.2, C66.1, D1.5, FB2.2, R4.2, R33.1, U10.1
/Sync In/Out/RXD: CON6.3, U6.105
/USB/EECLK: R2.1, U1.2, U2.62
/USB/EECS: R1.1, U1.1, U2.63
/USB/EEDATA: R6.2, U1.3, U2.61
/USB/EEDATA_OUT: R3.1, R6.1, U1.4
/USB/FTDI_1V8REG: C2.2, C3.2, C4.2, C15.1, U2.12, U2.37, U2.49, U2.64
/USB/FTDI_VPHY: C14.2, C17.1, FB4.2, U2.4
/USB/FTDI_VPLL: C8.2, C10.1, FB3.2, U2.9
/USB/GPIO_L0: R16.2, U2.43, U6.71
/USB/SPI_CLK: R15.1, U2.38, U6.70
/USB/SPI_DI: U2.40, U6.67
/USB/SPI_DO: U2.39, U6.68
/USB/VBUS_SENSE: R4.1, R5.2, U2.59
Earth: CON1.5, CON3.5, FB7.2
GND: C1.1, C2.1, C3.1, C4.1, C5.1, C6.1, C7.1, C8.1, C9.1, C10.2, C11.1, C12.1, C13.2, C14.1, C15.2, C16.1, C17.2, C18.1, C20.2, C21.2, C25.1, C26.1, C29.1, C30.1, C31.1, C32.1, C33.1, C34.1, C35.1, C36.1, C37.1, C38.1, C39.1, C40.1, C41.1, C42.1, C43.2, C44.2, C45.2, C46.2, C47.2, C49.1, C50.2, C51.2, C52.2, C53.2, C54.2, C55.2, C56.2, C58.1, C59.2, C60.2, C61.2, C62.2, C63.1, C64.1, C65.1, C66.2, C67.2, C68.1, C69.1, C70.2, C71.2, C74.1, C75.2, C76.1, C77.2, C78.1, C79.1, C80.2, C81.2, C82.1, C83.1, C84.2, CON6.2, CON7.1, D1.2, D8.3, FB1.1, FB6.1, FB8.2, MOD1.9, MOD1.10, MOD2.9, MOD2.10, MOD3.9, MOD3.10, MOD4.9, MOD4.10, MOD5.9, MOD5.10, MOD6.9, MOD6.10, MOD7.9, MOD7.10, Q1.1, Q1.4, Q2.2, R5.1, R10.1, R11.2, R12.2, R16.1, R26.1, R30.1, R32.2, U1.5, U2.1, U2.5, U2.10, U2.11, U2.13, U2.15, U2.25, U2.35, U2.47, U2.51, U3.2, U6.5, U6.13, U6.14, U6.59, U6.69, U6.86, U6.103, U6.132, U6.140, U7.4, U7.9, U8.4, U8.9, U9.2, U9.5, U10.2, U10.5, U11.2, U11.5, U12.2, U13.2, U14.6, U14.7, U14.21, X2.2, X2.4
GNDPWR: C72.1, C73.2, CON4.2, CON4.3, CON5.3, CON5.4, FB7.1, FB8.1, MOD1.15, MOD1.16, MOD1.17, MOD2.15, MOD2.16, MOD2.17, MOD3.15, MOD3.16, MOD3.17, MOD4.15, MOD4.16, MOD4.17, MOD5.15, MOD5.16, MOD5.17, MOD6.15, MOD6.16, MOD6.17, MOD7.15, MOD7.16, MOD7.17, R35.2
MOD1_PIN1: MOD1.1, U6.87
MOD1_PIN2: MOD1.2, U6.88
MOD1_PIN3: MOD1.3, U6.80
MOD1_PIN4: MOD1.4, U6.91
MOD1_PIN5: MOD1.5, U6.76
MOD1_PIN6: MOD1.6, U6.79
MOD1_PIN7: MOD1.7, U6.73
MOD1_PIN8: MOD1.8, U6.74
MOD2_PIN1: MOD2.1, U6.102
MOD2_PIN2: MOD2.2, U6.104
MOD2_PIN3: MOD2.3, U6.99
MOD2_PIN4: MOD2.4, U6.98
MOD2_PIN5: MOD2.5, U6.97
MOD2_PIN6: MOD2.6, U6.96
MOD2_PIN7: MOD2.7, U6.95
MOD2_PIN8: MOD2.8, U6.101
MOD3_PIN1: MOD3.1, U6.113
MOD3_PIN2: MOD3.2, U6.106
MOD3_PIN3: MOD3.3, U6.115
MOD3_PIN4: MOD3.4, U6.119
MOD3_PIN5: MOD3.5, U6.116
MOD3_PIN6: MOD3.6, U6.117
MOD3_PIN7: MOD3.7, U6.121
MOD3_PIN8: MOD3.8, U6.120
MOD4_PIN1: MOD4.1, U6.137
MOD4_PIN2: MOD4.2, U6.138
MOD4_PIN3: MOD4.3, U6.136
MOD4_PIN4: MOD4.4, U6.135
MOD4_PIN5: MOD4.5, U6.134
MOD4_PIN6: MOD4.6, U6.129
MOD4_PIN7: MOD4.7, U6.128
MOD4_PIN8: MOD4.8, U6.122
MOD5_PIN1: MOD5.1, U6.8
MOD5_PIN2: MOD5.2, U6.9
MOD5_PIN3: MOD5.3, U6.4
MOD5_PIN4: MOD5.4, U6.7
MOD5_PIN5: MOD5.5, U6.144
MOD5_PIN6: MOD5.6, U6.3
MOD5_PIN7: MOD5.7, U6.1
MOD5_PIN8: MOD5.8, U6.2
MOD6_PIN1: MOD6.1, U6.37
MOD6_PIN2: MOD6.2, U6.38
MOD6_PIN3: MOD6.3, U6.39
MOD6_PIN4: MOD6.4, U6.33
MOD6_PIN5: MOD6.5, U6.32
MOD6_PIN6: MOD6.6, U6.31
MOD6_PIN7: MOD6.7, U6.29
MOD6_PIN8: MOD6.8, U6.28
MOD7_PIN1: MOD7.1, U6.143
MOD7_PIN2: MOD7.2, U6.41
MOD7_PIN3: MOD7.3, U6.43
MOD7_PIN4: MOD7.4, U6.45
MOD7_PIN5: MOD7.5, U6.44
MOD7_PIN6: MOD7.6, U6.47
MOD7_PIN7: MOD7.7, U6.48
MOD7_PIN8: MOD7.8, U6.49
unnamed: C12.2, U2.2, X1.1
unnamed: C16.2, U2.3, X1.2
unnamed: C18.2, C20.1, F1.1, T1.15, U3.5
unnamed: C19.1, T1.9
unnamed: C19.2, U3.4
unnamed: C22.1, D2.3, U4.1, U4.3
unnamed: C23.1, D4.3, R13.2, U5.4
unnamed: C24.1, C85.2, U4.5, U5.2, U5.3, U5.8
unnamed: C27.1, C28.2, U6.35
unnamed: C27.2, C28.1, R14.1, U6.36
unnamed: C47.1, U7.8
unnamed: C48.1, L1.1, R24.2, U7.3
unnamed: C48.2, D6.3, U7.1
unnamed: C49.2, R24.1
unnamed: C56.1, U8.8
unnamed: C57.1, L2.1, R28.2, U8.3
unnamed: C57.2, D7.3, U8.1
unnamed: C58.2, R28.1
unnamed: C63.2, F2.1, R32.1, U9.4
unnamed: C64.2, F2.2, FB5.1
unnamed: C65.2, R33.2, R34.1, U10.3
unnamed: C80.1, R38.2, U14.3
unnamed: C83.2, C84.1, CON6.1, FB9.2
unnamed: CON1.1, FB2.1
unnamed: CON1.2, D1.4, R8.1
unnamed: CON1.3, D1.6, R9.1
unnamed: CON1.4, FB1.2
unnamed: CON2.2, U5.7
unnamed: CON2.3, U5.6
unnamed: CON3.1, FB5.2
unnamed: CON3.2, CON3.3
unnamed: CON3.4, FB6.2
unnamed: D2.1, D3.2, T1.1
unnamed: D2.2, D3.1, T1.3
unnamed: D4.1, T1.8
unnamed: D4.2, T1.6
unnamed: D5.1, R17.2, R20.1
unnamed: D5.2, R18.2
unnamed: D5.3, R19.2
unnamed: D9.3, Q3.1, R35.1
unnamed: Q1.3, T1.14
unnamed: Q1.6, T1.16
unnamed: Q2.3, R34.2
unnamed: R7.1, U2.14
unnamed: R8.2, U2.7
unnamed: R9.2, U2.8
unnamed: R10.2, U2.6
unnamed: R23.2, U7.6
unnamed: R25.1, R26.2, U7.5
unnamed: R29.1, R30.2, U8.5
unnamed: T1.11, U3.6
unnamed: U14.1, X2.1
unnamed: U14.2, X2.3

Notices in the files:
benchmarks/real_world/wiflier.kicad_pcb:
(C) 2014, 2015 C. Lohr
kicad files/spike_n_hold.kicad_pcb:
spike and hold circuit (2X) CERN OHL V2 S 20200202
